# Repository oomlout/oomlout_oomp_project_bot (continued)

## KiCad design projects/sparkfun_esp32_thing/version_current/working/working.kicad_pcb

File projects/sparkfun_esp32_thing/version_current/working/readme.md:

# OOMP Project  
## ESP32_Thing  by sparkfun  
  
oomp key: oomp_projects_flat_sparkfun_esp32_thing  
(snippet of original readme)  
  
SparkFun ESP32 Thing  
========================================  

[*SparkFun ESP32 Thing (DEV-13907)*](https://www.sparkfun.com/products/13907)  
  
The [SparkFun ESP32 Thing](https://www.sparkfun.com/products/13907) is a comprehensive development platform for Espressif’s ESP32, their super-charged version of the popular ESP8266. Like the 8266, the ESP32 is a WiFi-compatible microcontroller but adds nearly 30 I/O pins. The ESP32’s power and versatility will make it the foundation of IoT and connected projects for many years to come.  
  
Why the name? We lovingly call it the “Thing” because it's the perfect foundation for your Internet of Things project. The Thing does everything from turning on an LED to posting data with your chosen platform, and can be programmed just like any microcontroller. You can even program the Thing through the Arduino IDE by installing the [ESP32 Arduino Core](https://learn.sparkfun.com/tutorials/esp32-thing-hookup-guide-installing-the-esp32-arduino-core).  
  
The SparkFun ESP32 Thing equips the ESP32 with everything necessary to program, run and develop on the wonderchip. In addition to the WiFi SoC, the Thing includes an FTDI FT231x, which converts USB to serial, and allows your computer to program and communicate with the microcontroller. It also features a LiPo charger, so your ESP32 project can be battery-powered and truly wire  
  full source readme at [readme_src.md](readme_src.md)  
  
source repo at: [https://github.com/sparkfun/ESP32_Thing](https://github.com/sparkfun/ESP32_Thing)  
## Board  

## Schematic  

[schematic pdf](working_schematic.pdf)  
## Images

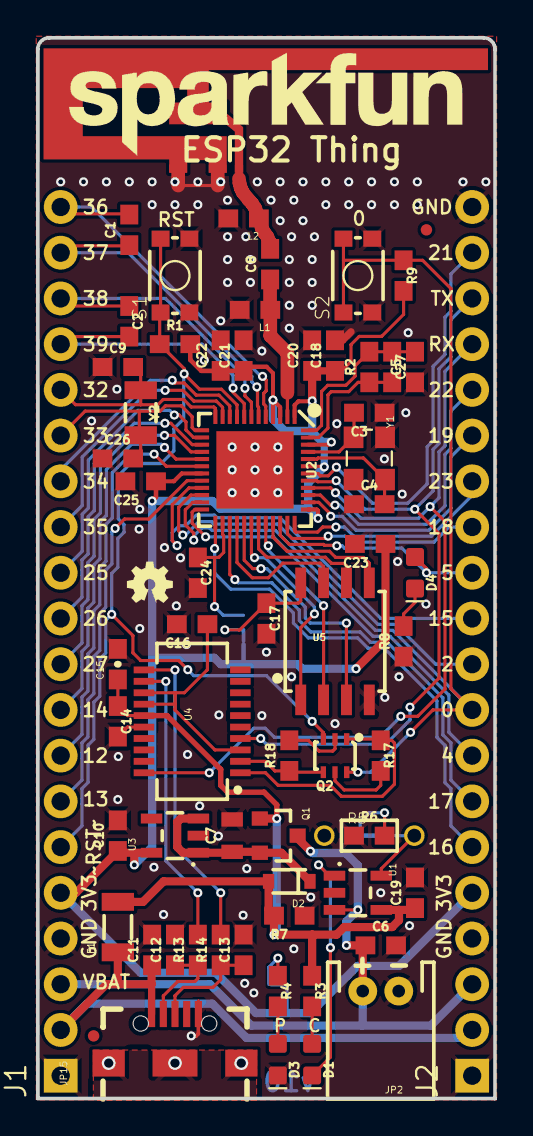
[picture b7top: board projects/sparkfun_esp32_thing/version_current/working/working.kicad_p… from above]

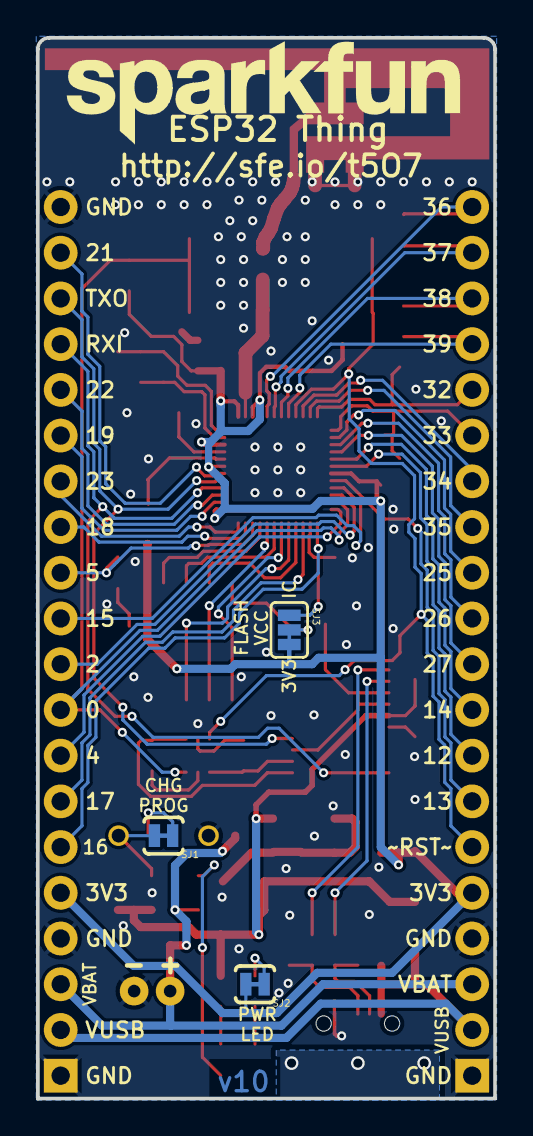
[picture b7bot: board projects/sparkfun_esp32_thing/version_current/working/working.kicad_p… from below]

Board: 2 copper layers, 25.4 x 58.9 mm, 72 parts (4 on the bottom side), 66 nets.

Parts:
C1, C2: 270pF; 0603
C3, C4: 10pF; 0603
C5: 10nF; 0603
C6, C19: 4.7uF; 0603
C7: 1.0uF; 0805
C8: 5.6pF; 0603
C9, C26: 15pF; 0603
C10: 2.2uF; 0603
C11, C14, C16, C17, C20, C21, C23, C25: 0.1uF; 0603
C12, C13: 47pF; 0603
C15: 4.7uF; 0603-CAP
C18: 100pF; 0603
C22: 10uF; 0603
C24: 1.0uF; 0603
C27: 3.0nF; 0603
D1: Yellow; LED-0603
D2: BAT20J; SOD-323
D3: RED; LED-0603
D4: BLUE; LED-0603
E1: ANTENNA; TRACE_ANTENNA_2.4GHZ_25.7MM_TUNED
F1: 500mA; PTC-1206
FD1, FD2: FIDUCIALUFIDUCIAL; MICRO-FIDUCIAL
FRAME1: FRAME-LEDGER; CREATIVE_COMMONS
J1, J2: 1X20_NOSILK
JP2: LiPo; JST-2-PTH
JP15: USB-B-MICRO-SMD_V03
L1, L2: DNP; 0603
LOGO1, LOGO3: SFE_LOGO_NAME.2_INCH; SFE_LOGO_NAME_.2
LOGO2: OSHW-LOGOMINI; OSHW-LOGO-MINI
Q1: 2.5A/30V; SOT23-3
Q2: MBT3904DW1T1; SC70-6
R1, R7, R9, R17, R18: 10k; 0603
R2: 20k; 0603
R3, R4: 1K; 0603
R5: DNP; 1_6W-RES
R6: 2.0k; 0603
R8: 330; 0603
R13, R14: 27; 0603
S1: RESET; TACTILE_SWITCH_SMD_4.6X2.8MM
S2: BTN-0; TACTILE_SWITCH_SMD_4.6X2.8MM
SJ1, SJ2: JUMPER-PAD-2-NC_BY_TRACE; PAD-JUMPER-2-NC_BY_TRACE_YES_SILK
SJ3: PAD-JUMPER-3-2OF3_NC_BY_TRACE_YES_SILK_FULL_BOX
U1: MCP73831; SOT23-5
U2: ESP3212; QFN48-0.4MM
U3: AP2112K-3.3V; SOT23-5
U4: FT231XS; SSOP20_L
U5: W25Q32FVSS; SOIC-8
Y1: 26MHz; CRYSTAL-SMD-3.2X2.5
Y2: 32.768kHz; CRYSTAL-SMD-3.2X1.5MM

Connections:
0: J2.9, Q2.6, R9.1, S2.3, S2.4, U2.23
2: J2.10, U2.22
3.3V: C10.1, C18.1, C20.1, C21.1, C22.1, C23.1, C25.1, J1.5, J2.5, R1.2, R9.2, SJ2.2, SJ3.3, U2.1, U2.3, U2.4, U2.19, U2.37, U2.43, U2.46, U3.5
3.3V_F: C16.1, U4.3, U4.13, U4.14
4: J2.8, U2.24
5: D4.A, J2.12, U2.34
12: J1.8, U2.18
13: J1.7, U2.20
14: J1.9, U2.17
15: J2.11, U2.21
16: J2.6, U2.25
17: J2.7, U2.27
18: J2.13, U2.35
19: J2.15, U2.38
21: J2.19, U2.42
22: J2.16, U2.39
23: J2.14, U2.36
25: J1.12, U2.14
26: J1.11, U2.15
27: J1.10, U2.16
32K_XN: C26.2, J1.15, U2.13, Y2.P$2
32K_XP: C9.2, J1.16, U2.12, Y2.P$1
34: J1.14, U2.10
35: J1.13, U2.11
36: C1.2, J1.20, U2.5
37: C1.1, J1.19, U2.6
38: C2.1, J1.18, U2.7
39: C2.2, J1.17, U2.8
CAP_10N: C5.2, C27.1, R2.2, U2.48
CHIP_PU: J1.6, Q2.3, R1.1, S1.3, S1.4, U2.9
D+: C13.1, JP15.D+, R14.1
D-: C12.1, JP15.D-, R13.1
DTR: Q2.1, R17.1, U4.1
FLASH_SCK: U2.31, U5.6
FLASH_SCS: U2.30, U5.1
FLASH_SDI: U2.33, U5.5
FLASH_SDO: U2.32, U5.2
FLASH_SHD: U2.28, U5.7
FLASH_SWP: U2.29, U5.3
FLASH_VDD: C24.1, SJ3.1, U2.26
GND: C3.1, C4.1, C5.1, C6.2, C7.2, C9.1, C10.2, C11.2, C12.2, C13.2, C14.2, C15.2, C16.2, C17.2, C18.2, C19.2, C20.2, C21.2, C22.2, C23.2, C24.2, C25.2, C26.1, D3.C, E1.GND, E1.GND2, J1.1, J1.4, J2.1, J2.4, J2.20, JP2.1, JP15.GND, L1.2, L2.2, R5.1, R6.1, R7.1, R8.1, S1.1, S1.2, S2.1, S2.2, U1.2, U2.EP, U3.2, U4.6, U4.16, U5.4, Y1.2, Y1.4
LNA_IN: C8.1, L1.1, U2.2
unnamed: D4.C, R8.2
unnamed: D3.A, R4.2
unnamed: R4.1, SJ2.1
unnamed: C27.2, R2.1, U2.47
unnamed: R13.2, U4.12
unnamed: R14.2, U4.11
unnamed: D1.C, U1.1
unnamed: Q2.5, R17.2
unnamed: C17.1, SJ3.2, U5.8
unnamed: Q2.2, R18.2
unnamed: C3.2, U2.45, Y1.1
unnamed: R5.2, SJ1.2, U1.5
unnamed: C4.2, U2.44, Y1.3
unnamed: R6.2, SJ1.1
unnamed: D1.A, R3.2
RTS: Q2.4, R18.1, U4.2
SHIELD: JP15.SHIELD1, JP15.SHIELD2, JP15.SHIELD3
TRACE_ANT: C8.2, E1.ANT, L2.1
U0RXD: J2.17, U2.40, U4.20
U0TXD: J2.18, U2.41, U4.4
VIN: C7.1, D2.C, Q1.2, U3.1, U3.3
VUSB-RAW: C11.1, F1.1, J1.2, J2.2, JP15.VBUS
V_BATT: C6.1, J1.3, J2.3, JP2.2, Q1.3, U1.3
V_USB: C14.1, C15.1, C19.1, D2.A, F1.2, Q1.1, R3.1, R7.2, U1.4, U4.15

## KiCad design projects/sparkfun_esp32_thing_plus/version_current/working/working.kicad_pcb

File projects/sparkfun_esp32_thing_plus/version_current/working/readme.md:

# ESP32_Thing_Plus by sparkfun  
This is a harvested standardized copy of a project from github.  
The original project can be found at:  
https://github.com/sparkfun/ESP32_Thing_Plus  
Please consult that link for additional, details, files, and license information.  
Note: It was auto harvested and if the original repo had more than one board file or anything out of the ordinary the files here are likely not representative.

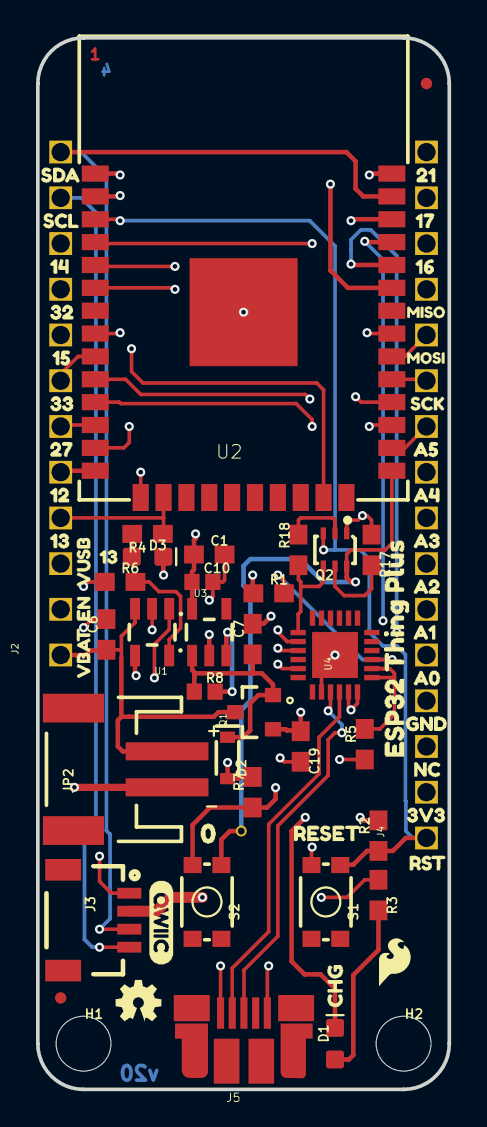
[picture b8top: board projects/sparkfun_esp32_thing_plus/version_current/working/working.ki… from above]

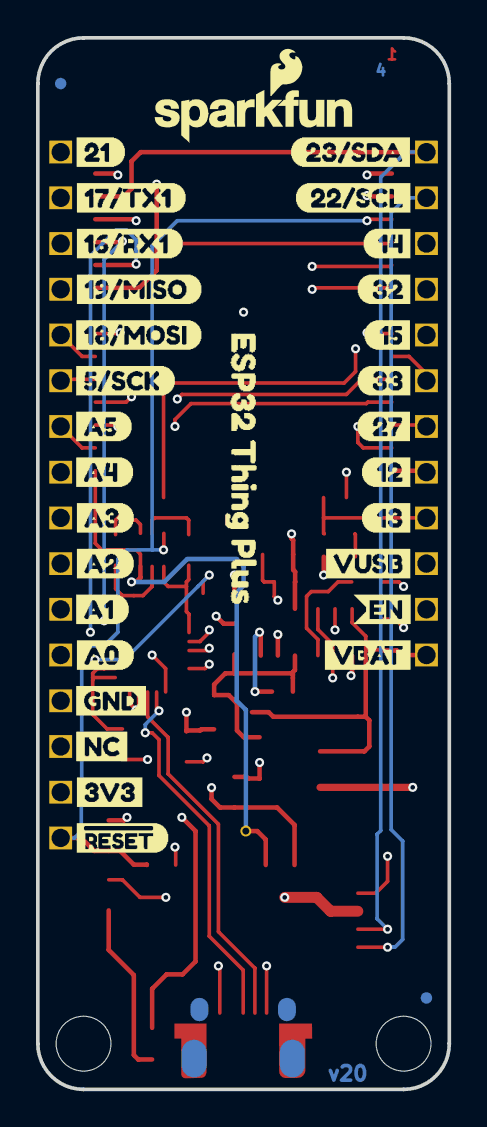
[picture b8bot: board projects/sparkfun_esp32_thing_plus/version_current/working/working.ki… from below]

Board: 4 copper layers, 22.9 x 58.4 mm, 107 parts (32 on the bottom side), 43 nets.

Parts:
C1: 10uF; 0603
C6, C19: 4.7uF; 0603
C7: 1.0uF; 0603
C10: 1.0uF; 0402
D1: Yellow; LED-0603
D2: 1A/23V/620mV; SOD-323
D3: BLUE; LED-0603
FD1, FD2, FD3, FD4: FIDUCIALUFIDUCIAL; FIDUCIAL-MICRO
FRAME1: FRAME-LEDGER; CREATIVE_COMMONS
H1, H2: STAND-OFFTIGHT; STAND-OFF-TIGHT
J2: 1X12_SM_SQ_NOSILK
J3: 1X04_1MM_RA
J4: 1X16_SM_SQ_NOSILK
J5: USB-MICROB-PTH-MILL
JP2: LiPo; JST-2-SMD
LOGO1: SFE_LOGO_FLAME.1_INCH; SFE_LOGO_FLAME_.1
LOGO2: OSHW-LOGOMINI; OSHW-LOGO-MINI
LOGO3: SFE_LOGO_NAME_FLAME.1_INCH; SFE_LOGO_NAME_FLAME_.1
LOGO4: FOUR_LAYER_WARNING
Q1: 2.5A/30V; SOT23-3@1
Q2: MBT3904DW1T1; SC70-6
R1, R4: 1k; 0603
R2, R7, R17, R18: 10k; 0603
R3: 1K; 0603
R5: 10; 0603
R6: 2.0k; 0603
R8: 100K; 0402
S1: RESET; TACTILE_SWITCH_SMD_4.6X2.8MM
S2: 0; TACTILE_SWITCH_SMD_4.6X2.8MM
TP1: TP_15TH
U1: MCP73831; SOT23-5
U2: ESP-WROOM-32NARROW; ESP-WROOM-32-NARROW
U3: AP2112K-3.3V; SOT23-5
U4: CP210X; QFN24
U$1: #RESET0
U$2: 3V31
U$3: 1323
U$4: 1417
U$5: 1519
U$6: 16#RX11
U$7: 17#TX10
U$8: 121
U$9: 210
U$10: 2721
U$11: 3218
U$12: 3320
U$13: A03
U$14: A14
U$15: A25
U$16: A36
U$17: A47
U$18: A58
U$19: EN26
U$20: GND2
U$21: 22#SCL1
U$22: 23#SDA0
U$23: QWIIC27
U$27: VBAT25
U$28: VUSB24
U$29: SDA1
U$30: SCL0
U$31: 142
U$32: 323
U$33: 154
U$34: 335
U$35: 276
U$36: 127
U$37: 138
U$38: 219
U$39: 1710
U$40: 1611
U$41: A515
U$42: A416
U$43: A317
U$44: A218
U$45: A119
U$46: A020
U$47: SCK20
U$48: GND21
U$49: NC22
U$50: VUSB8
U$51: EN9
U$52: VBAT10
U$53: 137
U$54: MISO0
U$55: MOSI1
U$56: CHG1
U$57: RESET0
U$58, U$65: ESP32_THING_PLUS0
U$59: ORDERING_INSTRUCTIONS
U$60: 3V323
U$61: RST24
U$62: 00
U$63: 5#SCK2
U$64: NC0
U$66: 18#MOSI1
U$67: 19#MISO0

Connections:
0: Q2.6, S2.4, TP1.P$1, U2.25
3.3V: C1.1, C10.1, J3.2, J4.2, R1.1, R2.2, U2.2, U3.5, U4.5, U4.6
12: J2.5, U2.14
13: J2.4, R4.1, U2.16
14: J2.10, U2.13
15: J2.8, U2.23
16: J4.14, U2.27
17: J4.15, U2.28
21: J4.16, U2.33
27: J2.6, U2.12
32: J2.9, U2.8
33: J2.7, U2.9
A0: J4.5, U2.11
A1: J4.6, U2.10
A2: J4.7, U2.6
A3: J4.8, U2.5
A4: J4.9, U2.4
A5: J4.10, U2.26
CHG: D1.C, U1.1
CHIP_PU: J4.1, Q2.3, R2.1, S1.4, U2.3
D+: J5.D+, U4.3
D-: J5.D-, U4.4
DTR: Q2.1, R17.1, U4.23
EN: J2.2, R8.2, U3.3
GND: C1.2, C6.2, C7.2, C10.2, C19.2, D3.C, J3.1, J4.4, J5.GND, JP2.1, R6.1, R7.1, S1.1, S2.1, U1.2, U2.1, U2.15, U2.38, U2.GND, U3.2, U4.2, U4.PAD
MISO: J4.13, U2.31
MOSI: J4.12, U2.30
unnamed: R1.2, U4.9
unnamed: D3.A, R4.2
unnamed: R5.2, U4.7, U4.8
unnamed: Q2.5, R17.2
unnamed: Q2.2, R18.2
unnamed: R6.2, U1.5
unnamed: D1.A, R3.2
RTS: Q2.4, R18.1, U4.19
RX: U2.35, U4.20
SCK: J4.11, U2.29
SCL: J2.11, J3.4, U2.36
SDA: J2.12, J3.3, U2.37
TX: U2.34, U4.21
VIN: C7.1, D2.C, Q1.2, R8.1, U3.1
V_BATT: C6.1, J2.1, JP2.2, Q1.3, U1.3
V_USB: C19.1, D2.A, J2.3, J5.VBUS, Q1.1, R3.1, R5.1, R7.2, U1.4
